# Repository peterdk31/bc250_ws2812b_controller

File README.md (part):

# Serial LED controller

A Linux daemon that renders WS2812 (NeoPixel) effects on the host and streams
the frames over USB serial to an ESP32, which just clocks them out to the strip.
All the logic — sensors, rules, effects — lives on the host, so changing
behavior never means reflashing the microcontroller.

Built for an AMD BC-250 running its case lighting from CPU temperature and load,
but nothing is board-specific. Co-authored with
[Claude](https://claude.com/claude-code) (Anthropic).

```
host (led daemon)                      ESP32              strip
sensors → rules → effect → frames ──serial──→ SPI/DMA ──→ WS2812
```

## Hardware

- An ESP32 or ESP32-C3 dev board over USB (`/dev/ttyUSB0` or `/dev/ttyACM0`).
  **Prefer the C3**: its native USB lets the firmware tell whether the host is
  actually running, so the boot animation also plays on reboots and on machines
  that keep standby power on their USB ports. A plain ESP32 can't see any of
  that over UART and only plays it after a true power cycle (see
  [How it works](#how-it-works)).
- A WS2812/WS2812B strip: data to the GPIO set as `strip.pin` (default 13), plus
  5 V and GND from a supply that can handle it (not the board's regulator; share
  grounds).
- Optionally, a momentary power button and a wire to the PSU's PS_ON# line —
  the receiver can then stand in for the PS_ON→GND jumper an ATX/FSP supply
  needs before it starts (see [Power switch](#power-switch)).
- For the BC-250 there is a small carrier PCB in
  [`hardware/bc250_carrier`](hardware/bc250_carrier/README.md): the C3 Super
  Mini solders onto it, the PSU's 10-pin Mini-Fit Jr plug goes straight onto
  a header, and the strip, button, sense wire and four PWM fan headers each
  get a labelled connector — the power switch, strip and fan wiring below, on
  one board.

## Getting started

Two things are needed on the host:

- **`g++` and `make`** to build the daemon. On CachyOS (or any Arch) they come
  in the `base-devel` package group.
- **`esptool`** to flash the receiver (plus `curl`, which is preinstalled).
  You do **not** need an ESP32 toolchain — `make flash` downloads a prebuilt
  firmware image.

```sh
sudo pacman -S --needed base-devel    # compiler + make
pipx install esptool                  # ESP32 flasher (or: pip install --user esptool)
```

On Bazzite (immutable base image) `esptool` installs the same way, but
`g++`/`make` aren't in the base image — build the daemon inside a distrobox,
or copy a prebuilt `led` binary over.

Then build, flash, and start:

```sh
sudo make install                            # daemon + systemd unit + default config
sudo make flash                              # download prebuilt firmware + flash the ESP32
sudo systemctl enable --now led-controller
```

`make flash` reads the chip (`target`, default `esp32c3`) and port
(`serial.port`) from the config; override on the command line, e.g.
`sudo make flash PORT=/dev/ttyACM0 TARGET=esp32`. It stops the service during the
write and restarts it after.

### The full BC-250 flash

Everything this repo can put on the receiver — the ATX power switch, the PWM
fans, the BLE phone remote — is described in the config, in the blocks
`power_switch`, `fans` and `ble_remote` (each has its own section below).
`make flash` bakes all three into the receiver's small settings partitions the
same way it already bakes `strip.pin`, so the full flash is the plain one:

```sh
sudo make flash
```

The config is `/etc/led-controller/config.json` when it exists, else the
repo's (`CONFIG=path` overrides). The shipped `power_switch` block is on,
with the carrier board's pins; the fan and BLE blocks ship off, and an
explicit `false` *is* written. For the power switch that matters: a receiver
whose switch is written off releases PS_ON# and cuts the machine's power (see
[Power switch](#power-switch)). Flashing from a config that has no
`power_switch` block at all leaves the chip's switch settings alone, so
delete the block, or keep it enabled, before flashing a machine whose power
already hangs on the receiver. Writing the features from one file also arms
the encoders' strictest cross-checks: a pin claimed by two blocks, or by a
block and `strip.pin`, is a hard error. Each feature's section has the `flash-pwr` / `flash-fan` /
`flash-ble` target that rewrites just that block in seconds.

Finally, edit `/etc/led-controller/config.json` for your hardware — at least
`strip.leds`, `strip.pin`, and `serial.port` — then `sudo systemctl
restart led-controller`.

To try an effect directly (stop the service first, it holds the port):

```sh
led /etc/led-controller/config.json rainbow
```

This runs unprivileged once the serial-group membership added by `make install`
is active — that takes effect on your next login; before then, prefix `sudo`.

## How it works

The daemon renders every frame and sends it over serial; the receiver only
displays what arrives. Pin and LED count travel in each frame, so the firmware
is generic and never needs reflashing for a config or effect change.

While the daemon isn't driving the line — at cold boot before it starts, and
after it exits on shutdown — the receiver plays a **boot** and **shutdown**
animation from flash. The daemon renders those too (through the same color
pipeline), records them, and uploads them once at startup; the receiver stores
them and replays them. So editing the boot/shutdown effects also needs no
reflash — just a daemon restart. A fresh, never-recorded board stays blank
until the daemon has run once and uploaded the recordings.

*When* the boot animation plays depends on the board. It always runs from chip
reset until the daemon's first frame. On USB-native chips (the C3 and friends)
it also re-arms whenever the USB host goes away and comes back — the bus
keepalives stop for a few seconds and return — which covers a reboot (shutdown
animation, dark while the host is down, boot animation as it comes back up)
and a power-on where standby VBUS kept the receiver running the whole time. A
plain ESP32's UART carries no trace of the host's state, so it shows the boot
animation only when it genuinely loses power; on a reboot it stays dark after
the shutdown animation until the daemon returns. If the power-on animation
matters to you, get a C3.

The serial baud auto-negotiates: if bytes arrive but no frame decodes, the
receiver cycles through the supported rates until frames validate, then
remembers the working rate in flash. Changing `serial.baud` just needs a
service restart.

## Flashing the receiver

The firmware is a native [ESP-IDF](https://docs.espressif.com/projects/esp-idf/en/stable/esp32/get-started/)
project under `firmware/` (no arduino-cli, no `.ino`). CI builds it for each
target and publishes merged images to GitHub Releases; `make flash` downloads
the one for `TARGET` and writes it — no toolchain needed.

```sh
sudo make flash                     # download prebuilt image + flash (default)
sudo make flash FW_RELEASE=v1.0.0   # pin a release instead of latest
```

The image is written at `0x0` and doesn't touch the NVS or LittleFS partitions,
so a reflash keeps a board's saved state.

**Building from source** is only needed to modify the firmware, or to bake a
non-default `serial.baud` / `host_timeout_ms` into it. It builds inside
Espressif's ESP-IDF container (needs `docker` or `podman` — nothing is installed
on the host, and `make receiver-clean` drops the cached image), or against a
native ESP-IDF if you set `IDF_PATH=...`:

```sh
sudo make flash-source              # build (container/native) + flash
make receiver                       # build only, no flash
```

**Clearing the board's saved state** — the reset switch when the receiver acts
as if it remembers something wrong. Each erases one partition region; the app
and the power-switch wiring (`pwrcfg`) are untouched:

```sh
sudo make clear-nvs                 # remembered baud + strip geometry
sudo make clear-recordings          # stored boot/shutdown animations
```

The daemon re-uploads the recordings on its next start (and the receiver
re-formats the partition), so `clear-recordings` is also how you get past a
stale or half-written slot that the skip-unchanged hash check would otherwise
keep. As with flashing, esptool resets the chip — see the caveat under
[Power switch](#power-switch).

### Receiver debug log

The receiver has no console (the link is the daemon's), so it keeps a small log
ring in RAM and hands it back over the link on request. Set

```jsonc
"serial": { "debug_log": true }
```

and its lines appear in `journalctl -u led-controller` — the recording uploads
and where they went, boot/shutdown replays, host-gone/host-back transitions, the
strip blanking on timeout, and the power switch's own decisions. The ring is in
RAM on a board running from 5VSB, so events logged while the host was down (a
follow-down, a boot replay) drain once the daemon is back. With the flag off the
daemon never asks and the receiver never sends a log line — the only thing it
ever says unprompted is a power-button request (see
[Power switch](#power-switch)).

## Configuration

`/etc/led-controller/config.json`. The first half describes the receiver — the
chip, the link, and everything it does on its own when the daemon isn't
running — the second half the host's rendering:

```jsonc
{
    "target": "esp32c3",        // chip to build/flash for (esp32, esp32c3, ...)
    "serial": {
        "port": "/dev/ttyUSB0", // "none" or "" (or LED_PORT=none) runs headless;
        "baud": 921600,         // omitting the key defaults to /dev/ttyUSB0
        "debug_log": false      // drain the receiver's log to journalctl
    },
    "host_timeout_ms": 5000,    // receiver blanks after this long with no frame —
                                // baked into the firmware by `make flash-source`
                                // only; the prebuilt image always uses 5000
    "power_on": { ... },        // boot/shutdown animations the receiver replays
    "shutdown": { ... },        // (standalone effects only, see below)

    "power_switch": {           // the ATX power button, see Power switch
        "enabled": true,            // enabled + pins: flash-time (make flash-pwr)
        "hold_seconds": 2,          // hold this long for a hard cut     ┐ the four tunings:
        "boot_timeout_seconds": 10, // rail not up by then = release PS_ON# │ live (reload, or
        "sense_low_mv": 800,        //                                     │ the phone's cog
        "sense_high_mv": 2000,      //                                     ┘ on the Power tab)
        "pins": { "ps_on": 3, "button": 1, "button_gnd": null, "sense": 2, "led": 8,
                  "wake": null },   // wake: an OpenPuck's power-on pulse, see Power switch
        "short_press": "systemctl poweroff" // what the daemon runs on a short
                                    // press; null = ignore it
    },
    "ble_remote": {             // the phone power button + dashboard, see BLE remote
        "enabled": false,
        "name": "BC250",
        "token": ""                 // 8-16 chars; readable by anyone with a shell here
    },
    "fans": [                   // the fans, see Fans — each an input, a curve
        { "name": "pump", "output": "header1",               // and an output (a receiver
          "input": "fallback", "fallback": 65, "boost": 100 }, // header, a pin, or the
        { ... }                                              // host's own pwm output)
    ],

    "strip": {
        "leds": 58,
        "pin": 13,              // ESP32 GPIO driving the strip
        "reverse": false,       // flip so LED 0 is at the far end
        "brightness": 0.2,      // 0..1, linear
        "gamma": "2.2",         // one value, or three ("2.0 2.2 2.4") per R/G/B
        "white_balance": "ffb0f0" // RRGGBB neutral-white gain; ffffff = off
    },
    "sensors": [ ... ],         // hwmon candidates, see Sensors
    "rules": [ ... ]
}
```

Configs from before September 2026 had an `esp32` block and a `sinks.serial`
one; the daemon names the old key and what it became, and exits, rather than
run on a half-read file.

### Checking a config

```sh
led --check /etc/led-controller/config.json   # or: make check
```

Would the daemon start on this file, and is it the file you meant to write?
The check parses it and runs every block through the same validation the
daemon does at startup — retired keys, the fans block, the rules and their
conditions and effect names, the boot and shutdown recordings (rendered, so a
segment that can't record is caught here) — and then the things the daemon
would run on but nobody could have intended: a key that isn't one inside
`serial`, `strip`, `power_switch`, `ble_remote`, a rule or a recording
segment (with a "did you mean" for a near miss), a value of the wrong type, a
color that isn't `RRGGBB`, a LED count over the receiver's 100, an inverted
sense hysteresis, an enabled `ble_remote` without a token. Each is a line
naming the key; any of them fails the check (exit 1). A `note:` line is
something to look at that may be intended — a top-level key the daemon
doesn't read by name (effects see every top-level key as a shared default
setting), or a rule below a catch-all that can never be reached — and
doesn't fail it. It opens no port and sends nothing; the sensor lookups only
say "not found yet" on a box without them.

`make install` runs the check on the deployed file with the freshly built
daemon before it swaps the binary and restarts the service, so a key the new
version retired is reported while the old daemon still runs, not as a crash
loop after; `make install CHECK=0` skips that.

### Live reload

The running daemon watches its config file and picks up a save within a
second or two — rules, effects, sensors, strip settings, the fans block —
with no restart. A change confined to the `fans` or `power_switch` blocks
leaves the running effect alone; anything else drops the current effect and
the matching rule starts afresh (a crossfade on the strip, like any other
switch). `systemctl reload led-controller` (SIGHUP) does the same
immediately. A file that doesn't parse or validate is reported in the journal
and the running config is kept, so a typo costs a log line rather than a
crash loop; fix it and save again. Two things still need more than a reload:
the `serial` block, because the port is opened once (the daemon says so when
it changes; restart), and anything flash-time on the receiver — the power
switch's pins and enable, the board's fan header map, `ble_remote` — which
is `make flash`'s business (the fans' outputs are not: a reload moves them). The power switch's four tunings and `short_press` are
not flash-time: a reload pushes the tunings to the receiver and changes what
a press does at once. Editing `power_on`, `shutdown` or `strip` re-renders
and re-sends the boot and shutdown recordings, which holds the strip for
about a second. Edits from the phone's dashboard take a shorter path: they
are applied live and written into the file by the daemon itself (`fans`,
`strip`, a scene rule's `color`/`level`, the `power_switch` tunings and
`short_press`), which then treats the file's new mtime as its own doing
rather than a change to reload.

### Tuning the colors

`brightness`, `white_balance`, and `gamma` fold into one per-channel lookup
table applied on the host, so they cost nothing per frame.

How to read the values — every knob is per-channel, red green blue:

```
white_balance "b4b0f0"          gamma "1.9 1.8 1.7"
               ││││└┴─ blue            └┬┘ └┬┘ └┬┘
               ││└┴─── green          red green blue
               └┴───── red
```

Two rules cover every adjustment:

- **White balance scales a channel the same at every level.** Lower a pair →
  less of that color, from full white down to the dimmest glow. `ff` = leave
  the channel alone.
- **Gamma changes how a channel *fades*.** A higher number makes that channel
  die away faster as colors dim; full-on and off never move. `2.2` is
  neutral; you only need three different numbers when a tint appears *only*
  at low levels.

So: name the color the white is leaning toward, then move that channel —
down in `white_balance` if the tint is there at full brightness, up in
`gamma` if it only creeps in as things get dim.

Dial the knobs in by symptom, in this order:

1. **Everything too bright or dim for the room** → `brightness` (0..1).
2. **Full white looks tinted** → `white_balance`: lower the channel(s) of
   the tint. White leans green → lower the middle pair (`ffb0f0`). This is
   the strip+diffuser calibration; start from the diffuser table below.
3. **Full white is neutral, but dim white picks up a tint** →
   per-channel `gamma`: raise the tint's channel so it fades faster (dim
   white leans blue → `"2.2 2.2 2.4"`) — or equivalently lower the channel
   that's going missing (dim white leans blue because red drops out →
   `"2.0 2.2 2.2"`).

The `solid` effect exists for exactly this — it puts up a fixed test field
through the normal correction pipeline:

```bash
led /etc/led-controller/config.json solid    # full white: judge white_balance
```

Look, adjust the config, run again. For the gamma step you need *dim* white;
a forced effect has no rule settings, but effects fall back to top-level
config keys, so temporarily add `"level": 0.25` at the top level of the
config (next to `"strip"`) and run `solid` again. Remove it when done.

**From the couch, with the BLE remote:** the shipped config's first rule is
the same test field as a switch — a static color with a level, which doubles
as a plain light when it isn't tuning anything —

```jsonc
{ "if": "file:/tmp/led-static-color", "effect": "solid", "hold": 0,
  "settings": { "color": "ffffff", "level": 1.0 } }
```

— and the phone's dashboard shows every such `file:` rule as a **scene**
with a switch (README [BLE remote](#the-dashboard)). Switch "solid" on, drag
the white-balance sliders on the LEDs tab while looking at the strip
(each release applies to the live strip at once and lands in the config's
`strip` block), pull the scene's `level` slider down for the gamma step,
switch it off. The color picker on the scene changes the rule's `color`, so
the same switch tests a pure red or a warm white. Any `file:` rule with a
`color` or `level` setting gets the same controls; one without is just a
switch (the `/tmp/led-night` rule below, say). Put these rules first so they
win over everything else while on.

`white_balance` is the *total* correction — strip and diffuser combined into
one measured value. Starting points per diffuser (always confirm against
`solid` white):

| Diffuser | `white_balance` | Why |
|---|---|---|
| none / clear cover | `ffb0f0` | just the strip's own green excess |
| white (milky) | `ffb0f0` | near-neutral filter; scatters but barely tints — trim blue a touch (`ffb0e0`) if white reads cool |
| black / smoked film | `b4b0f0` | dark film passes red most, so take the bare-strip value and pull red down ~30% on top of it. Films vary a lot: one measured black window film landed at `b4ffff` instead — its green/blue cut cancelled the strip's own green excess. Pair with per-channel gamma (e.g. `"1.9 1.8 1.7"`) if dim white still drifts |

Low brightness costs no smoothness: the corrected values ride the wire with 8
extra fractional bits and the receiver rounds them away with a temporal dither
at its own strip-refresh rate (several hundred Hz — far above flicker fusion),
so dim gradients glide instead of stepping or shimmering. There is nothing to
configure; the old `dither` key is gone (this needs receiver firmware from the
same version — reflash once after updating). A change to `strip` re-renders
the boot/shutdown recordings so they carry the new colors — on a hand edit as
part of the reload, after a phone edit ten seconds after the last slider
moved (each re-render holds the strip for about a second).

### Sensors

`sensors` is an ordered list of `chip:label` hwmon candidates; the first present
wins (a bare chip name means its `temp1_input`). Used by `temp` conditions.
The daemon keeps rescanning until one appears. The default
covers the BC-250 (`k10temp:Tctl`, then the NCT6686D under either nct driver).
Two more kinds of candidate take the same slot: `pmbus:CPU VRM` / `pmbus:GPU VRM`
read the BC-250's VRM controller over I2C, and `file:/path` reads a file
holding one temperature — both described under [Fans](#fans), where they are
also fan sources.

### Rules

Evaluated top to bottom every 0.5 s; the first rule whose `if` holds wins. A rule
without `if` always matches (put a catch-all last). No match → strip dark.

```jsonc
{
    "if": "proc:gamescope & temp>75",
    "effect": "ember",
    "hold": 5,                       // min seconds since last switch (default 0)
    "for": 3,                        // condition must hold this long to count (default 0)
    "settings": { "speed": 1.4 }     // effect-specific
}
```

Switches crossfade over the top-level `crossfade_ms` (default 600; 0 =
instant). `for` is an on-delay on the condition: it has to have held for that
many seconds before the rule matches, so a brief load spike never starts a
load rule. Dropping out is immediate. `hold` is the blunter guard: no switch
*into* this rule until that long after the last switch, whatever the
conditions did meanwhile.

### Conditions

| syntax | true when |
|---|---|
| `always` | always |
| `temp>N` / `temp<N` | sensor temperature above/below N °C |
| `cpu_load>N` / `cpu_load<N` | CPU busy above/below N % (bare `cpu_load` = `>20`) |
| `gpu_load>N` / `gpu_load<N` | amdgpu busy above/below N % (bare `gpu_load` = `>20`) |
| `proc:NAME` | a process with that name is running (15-char kernel limit) |
| `steam_dl` | a Steam download is actively moving bytes |
| `steam_launch` | a game launch is in a counted step — processing Vulkan shaders, verifying files (needs the debug port) |
| `steam_achievement` / `steam_achievement<N` | a Steam achievement unlocked in the last 5 / N seconds (needs the debug port) |
| `audio_playing` | system audio is actually playing (see below) |
| `file:/PATH` | the file exists |
| `!COND` | negation |
| `A & B` | both hold |
| `A \| B` | either holds (`&` binds tighter; no parentheses) |

`file:` is the external control surface — `touch /tmp/led-night` to switch modes,
`rm` to switch back. A rule whose whole condition is one `file:` path is also
a **scene** on the phone's dashboard ([BLE remote](#the-dashboard)): a switch
the daemon flips by creating or removing that file, with a color picker or a
level slider when the rule's settings carry `color` or `level`.

The `progress` effect turns the strip into a live progress bar for whichever
`"source"` its settings name — `steam_dl` (a download) or `steam_launch` (a game
launch processing its shaders) — with a celebration pulse at 100%. The rule's
condition is the same name, so the bar shows exactly while there's something to
show; give each its own palette (the default config does) to tell them apart.
`STEAM_FAKE_PERCENT` / `STEAM_FAKE_LAUNCH` preview them without Steam: a number
holds a static bar, `ramp20` climbs 20 %/s and celebrates.

Downloads work without the debug port too (percent driven by network
throughput). Reading other
users' Steam libraries needs the daemon running as root (the systemd unit does).
Each app of an install (the game, Steamworks redistributables, Proton, shader
pre-cache) fills its own bar, one after the other.

For exact progress the daemon reads Steam's own numbers — the ones its Downloads
page shows — over Steam's remote-debugging port, `"steam_debug_port": 8080` (on
by default; `null` turns it off). That needs Steam's remote debugging on: an
empty `.cef-enable-remote-debugging` file in the Steam directory
(`~/.local/share/Steam/`), which `make install` creates for every Steam user
while the key is set (Decky Loader creates it too). Restart Steam once after.
`make steam-debug-uninstall` (also part of `make uninstall`) removes the files
`make install` created, never one that was already there; set the key to `null`
as well, or the next install puts them back.

The debug port also feeds `steam_launch` (the launch dialog's counted steps) and
`steam_achievement`: Steam's own unlock toast, counted by the daemon's hook,
plays the `achievement` effect — a bloom at `origin` throwing a gold front along
the strip, glinting, then easing to dark. An unlock fewer than `rare_below` % of
players have burns in `rare_palette` instead. `STEAM_FAKE_ACHIEVEMENT=6` fires
a fake unlock every 6 s (every other one rare). `led <config> --steam-status`
shows what the hook sees, and which of Steam's functions a Steam update took
away.
The bar then follows Steam's percent, and a pause or finish shows at once. It uses
Steam's internal JS API (the one Decky plugins use), so a Steam update can break
it; whenever the port doesn't answer the daemon falls back to the estimate above
and says so in the journal. The port is localhost-only, but anything running on
the machine can drive the Steam client through it. `led <config> --steam-status`
shows which source is in use and what Steam reports.

The `audio_*` effects visualise what's playing (combine them with `cycle` for
variety — they share one capture stream and auto-gain, so hopping between them
is seamless). The effects capture samples by spawning `parec` (or
`pw-record`) on the default sink's monitor while active; running as root
(the systemd unit does) lets it find the user session's PipeWire socket under
`/run/user/`.

The `audio_playing` condition costs nothing while the system is silent (one
procfs read per tick). Once anything is audible it asks the sound server for
its playback stream list (`pactl -f json list sink-inputs`, spawned
asynchronously about once a second): an uncorked stream means playing, corked
or none means paused/stopped. That verdict is immune to quiet passages inside
the music and reacts to pause/resume within a second or two. It is also the
only source of truth: if the list can't be fetched while audio is audible
(no `pactl`, no reachable session), the condition stays false and a note is
left on stderr. Placing the rule *below* the `load` rule means load takes the
strip whenever it's active and music has it otherwise — first matching rule
wins.

## Effects

| name | description | key settings (defaults) |
|---|---|---|
| `alarm` | urgent heartbeat throbbing from the center | `color` (ff0000), `pulses_per_second` (2) |
| `audio_music` | audio-reactive bloom from the center: loudness sets its reach, bass pumps it and sends crests to the tips | `palette` (4a00b4,e02090,ff9c28), `pulse` (0.8), `gain_seconds` (6) |
| `audio_ripple` | audio-reactive: each bass hit sends a wave crest with a luminous wake racing from the center to the tips, reflecting back off them, colors walking the palette per beat | `palette` (0030a0,00c0e0,8040ff), `travel_seconds` (1.0), `sensitivity` (1.0), `reflect` (0.6) |
| `audio_spectrum` | audio-reactive liquid analyzer: a spring-loaded bar grows from the strip start with the loudness, a meniscus shine on its tip, bass pumping its base and treble its tip, a peak dot falling back with a comet tail between hits | `palette` (00e6b4,3a56ff,ff2e88), `pump` (0.7), `bounce` (0.6), `peak_color` (ffffff) |
| `achievement` | one shot: a bloom throws a glinting gold front along the strip, then eases to dark; rare unlocks in their own palette | `palette` (ff8a00,ffc040,fff0b0), `rare_palette` (ff3cac,8a4bff,38c8ff), `rare_below` (10), `origin` (0.5) |
| `aurora` | slow drifting color curtains walking a palette | `palette` (10ff80,10a0ff,8040ff), `speed` (1.0) |
| `boot` | calm bloom from the center into a full wash, then exhales into a dim hold | `intro_seconds` (7), `color` (ffffff) |
| `breathe` | palette wash on a slow breath with a drifting bright band | `palette` (0d4a44,30e090), `period_seconds` (3.5) |
| `button_off` | experimental: the lit strip collapses into the power button | `duration_seconds` (1.4), `color` (ffffff), `reverse` (true) |
| `button_on` | experimental: light spills out of the power button, then pulses | `spread_seconds` (2.5), `period_seconds` (4), `color` (ffffff) |
| `caustics` | underwater light caustics: two multiplied noise fields carve bright wandering filaments that merge and dissolve | `palette` (020818,004060,00b0c0,a0fff0), `sharp` (1.5), `gain` (3.2) |
| `comet` | Larson scanner with a fading tail, optional mirror | `palette` (8040ff,30c0ff), `sweeps_per_second` (0.7), `tail_pixels` (8) |
| `cycle` | rotates through a list of other effects | `period_seconds` (30), `effects` (list) |
| `drift` | soft palette glows wandering over a dark base | `palette` (2858ff,30d0b0), `blobs` (3), `speed` (1.4) |
| `ember` | slow warm aurora-style flow through an ember palette | `palette` (2a0a00,ff7d1e), `speed` (1.4) |
| `ink` | drops of ink recolor the whole strip in slow sweeping fronts, a glistening rim on each leading edge | `palette` (6a00ff,0080ff,00d0a0,ffb000,ff2060), `period_seconds` (10), `spread_seconds` (4) |
| `lava` | lava lamp: soft blobs drift, meet and merge into hotter spots | `palette` (ff0050,ff5a00,ffd000,00e5ff,7a00ff,ff00d0), `blobs` (4), `speed` (5.0) |
| `load` | CPU/GPU bars from center over a palette wash, each with a heartbeat that quickens under load; each side's palette window slides toward the hot end with its load | `palette` (00e0c0,2060ff,a040ff,ff4060,ff9000), `heat_span` (0.45), `color_drift` (0.3), `pulse` (0.5) |
| `load_boil` | CPU/GPU load as a lava lamp: each half's blobs boil harder and shift toward the palette's hot end with that side's load | `palette` (00e0c0,2060ff,a040ff,ff4060,ff9000), `blobs` (2), `boil` (2.5) |
| `orbit` | binary stars: glow pairs orbit a shared center, whipping through conjunctions that bloom white-hot | `palette` (1030ff,00d0ff,c080ff,ff40a0), `pairs` (2), `origin` (0.5) |
| `pendulum` | pendulum wave: each LED swings once more per period than its neighbour, so the strip drifts from one shared swell through travelling waves and braids and marches back into step | `palette` (2040ff,00d0c0,a040ff,ff4090,2040ff), `period_seconds` (60), `swings` (15), `origin` (0.0) |
| `plasma` | drifting sines + noise walking a palette | `palette` (0040ff,00d0a0,c040ff,0040ff), `speed` (1.4) |
| `progress` | live progress bar for a `source` (`steam_dl`, `steam_launch`), pulse at 100% | `source` (steam_dl), `palette` (d4009c,ff5a1e,ffd23c), `done_color` (00ff66) |
| `pulse` | soft palette rings expanding from the center | `palette` (5028ff,30d0ff), `period_seconds` (4) |
| `rainbow` | scrolling hue cycle with shimmer | `cycles_per_second` (0.9) |
| `shoreline` | waves roll in from both ends, decelerating and whitening into foam as they break at the center | `palette` (003048,00a090,60e0c0), `period_seconds` (6), `foam_color` (ffffff) |
| `shutdown` | CRT-style collapse to a point, then a slow phosphor fade | `duration_seconds` (5.0), `color` (0028ff) |
| `silk` | tide through a drifting warp field: color bands stretch, buckle and fold like fabric in a breeze | `palette` (3a1078,c03080,ff9040,20b0c0,3a1078), `fold` (0.5), `sheen` (0.3) |
| `solid` | fixed color everywhere — the color-calibration test field, or a plain static light | `color` (ffffff), `level` (1.0) |
| `tide` | a palette gradient sliding and breathing | `palette` (102060,1890d0,30d0a0,8040ff,102060), `speed` (1.4) |

Colors are `"RRGGBB"` or `"#RRGGBB"`; a `palette` is several separated by
non-hex (`"2a0a00, ff7d1e"`), spaced evenly and blended in RGB. Every effect
also takes `frame_ms` (delay between frames; default 16 ≈ 60 fps).
Settings resolve per-rule first, then top-level config, then the defaults above.

### Boot & shutdown animations

Set `power_on` / `shutdown` to any standalone effect, or a `sequence` played
into one recording — typically a one-shot intro into a looping idle:

```jsonc
"power_on": {
    "sequence": [
        { "effect": "boot",    "record_seconds": 4,
          "settings": { "intro_seconds": 3, "color": "ff7818" } },
        { "effect": "breathe", "record_seconds": 5, "loop": true,
          "settings": { "palette": "2a0a00,ff7818", "period_seconds": 5 } }
    ]
},
"shutdown": { "effect": "shutdown", "settings": { "color": "0028ff" } }
```

The last segment's `loop` decides the tail (loop from its first frame, else hold
the last frame); earlier segments play once. For a seamless loop make the
looping segment's `record_seconds` a whole multiple of its period. The whole
recording replays at one rate — the first segment's `frame_ms` — so a later
segment's own `frame_ms` has no effect on replay. Finite
effects (`shutdown`) record to completion; open-ended ones (`boot`) record for
`record_seconds`. Unchanged recordings aren't rewritten to flash (a hash is
compared), so wear is near zero. `cycle` can't be a slot (it needs the JSON
config).

Preview a slot exactly as the receiver will replay it, without hardware:

```sh
make virtual-strip && ./virtual-strip                    # one terminal
LED_PORT=none ./led config.json --preview power_on       # another
```

## Power switch

An ATX/FSP supply (like the BC-250's FSP500-30AS) doesn't start until its
PS_ON# line (the green wire) is pulled to ground — normally a permanent
jumper. With the receiver powered from the PSU's **5VSB** standby rail, it can
drive that line instead and act as the machine's power button
(after [Thunkar/bc250-esp32-switch](https://github.com/Thunkar/bc250-esp32-switch),
minus its WiFi/BLE):

- **Press** the button while off → PS_ON# is sunk to ground, the PSU starts,
  the board boots. It fires on the press itself, not on the release, so that
  keeping it held afterwards is free to mean the failsafe below.
- **Short press** while the machine is up → the ordinary PC power-button
  gesture: the OS is asked to shut itself down gracefully. The receiver can't
  do that itself, so it asks over the link and the daemon runs the
  `power_switch.short_press` command (`"systemctl poweroff"`); the machine
  then powers itself off and the sense wire's follow-down releases PS_ON#.
  With `short_press` set to `null` the press is ignored (and the journal
  says so). If nobody answers within 3 s
  — daemon down, no OS yet, feature off — the request is dropped and the
  feedback LED blinks fast for a moment, because otherwise an unheard press
  looks exactly like a broken button. Nothing about this path touches PS_ON#:
  the worst case is a machine that stays on.
- **Hold** for 2 s while on → PS_ON# is released — a hard power-off for a
  wedged machine, and the answer to an OS that accepts the graceful request and
  then hangs. (Only a press that began while the machine was already up can do
  this: the press that powered it on never turns it back off, however long it's
  held.)
- With the **sense** wire (BC-250: TPMS1 pin 9, ~2.9 V while the board is
  up): a graceful OS shutdown is followed down (the sense line drops, the
  receiver releases PS_ON# so the PSU turns off too), and a board that never
  comes up within 10 s releases the PSU instead of leaving it energized.
  The wire is optional but strongly recommended — without it both are
  skipped, and after every OS shutdown the PSU stays energized, holding
  PS_ON#, until a 2 s long-press; what's left is less a power button than a
  toggle that sticks on.
- **Keep holding the button** → the failsafe: while it is physically held the
  sense line cannot power anything off. Follow-down is suppressed, and the boot
  timeout is parked, counting its 10 s from the release instead of from the
  power-on. This is the way out of a mis-wired sense line, which is otherwise
  self-sealing: a sense pin that reads low while the board is really up (wrong
  pin, wire fallen off, thresholds wrong) makes the boot timeout cut the PSU
  ~10 s into every boot, so the machine can never stay up long enough to
  reflash the config that would fix it. Press to power on, keep your finger
  down, and the machine stays up while you reflash — including *through* the
  reflash: a receiver that comes up with the button already held adopts that
  press as the failsafe, and won't read it as a fresh 2 s force-off either.
  The sense line is still sampled and logged while held (see the debug log
  below) — that log is how the right pin and thresholds get found.

Wiring (the shipped `power_switch.pins`, for the ESP32-C3; `null` = not wired):

| receiver pin | connects to |
|---|---|
| GPIO3 (`ps_on`) | gate of an N-channel MOSFET that sinks PS_ON# to ground (see note below) — **not** PS_ON# directly |
| GPIO1 (`button`) | momentary switch terminal A (internal pull-up, pressed = low) |
| `button_gnd`: `null` when the switch is wired to a real GND (the carrier board), else e.g. GPIO21 | switch terminal B — driven low as a local ground, so the button needs no run to a real GND. (GPIO21 is U0TXD: free while the host link is USB) |
| GPIO2 (`sense`, `null` = not wired) | optional board-power sense, e.g. BC-250 TPMS1 pin 9, which is the board's main **3.3 V rail**. Emphatically *not* pin 15 (`3VSB`): that stays up whenever PS_ON# is held, so it reads like a working sense wire and then never fires follow-down or the boot timeout. Read as an averaged ADC voltage with hysteresis (`sense_low_mv` / `sense_high_mv`); the ADC saturates near 3.1 V, so a healthy rail logs ~2.9–3.1 V |
| GPIO8 (`led`, `null` = none) | optional feedback: the board's own little LED *blinks* while the button reads pressed (and through a wake pulse), so the wiring can be eyeballed without a PSU. GPIO8 is the plain onboard LED on common C3 dev boards; a blink shows regardless of the LED's polarity |
| `wake` (`null` = not wired; GPIO20 on the carrier's J11) | optional **wake input**: a 3.3 V active-high pulse from another device that wants the machine on — see *Waking from an OpenPuck* below. Internal pull-down; a rising edge while OFF powers on, and a pulse in any other state is dropped, so it can never shut anything down. Because it can do nothing else, this is the one pin that also **moves at runtime**, like the tunings: the daemon pushes `pins.wake` at startup and on a reload, and the phone's power settings pick it from the receiver's free pins (see [The dashboard](#the-dashboard)) |
| 5VSB + GND | PSU standby rail, so the receiver runs while the machine is off — **read the warning below before also plugging in USB** |

> ⚠️ **Critical — 5VSB and USB at the same time.** In this role the receiver
> is powered from 5VSB *and* still plugged into the host's USB for the LED
> link. That is two hard-paralleled 5 V supplies: most dev boards tie the USB
> connector's VBUS straight to their 5 V pin, so whichever rail sits higher
> pushes current into the other with nothing to limit it. Whenever the
> machine is off — the normal state for a power button — that means the
> receiver back-feeds the host's **dead** USB port continuously: current
> flows backwards through the port's VBUS circuitry (which is not designed
> for it and can be damaged) and phantom-powers part of the motherboard's
> 5 V rail off the PSU's small standby supply. **Cut or unpin the 5 V wire
> (red) in the USB cable**; keep D+, D− and GND. The receiver then runs
> solely from 5VSB and USB still works fully as a self-powered device —
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
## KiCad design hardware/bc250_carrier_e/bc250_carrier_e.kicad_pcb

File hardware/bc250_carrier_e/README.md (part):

# BC-250 carrier board (rev E)

Rev E is the same carrier as [rev D](../bc250_carrier/README.md), with the same
parts, nets and firmware, laid out differently: **every plug sits on the left,
the PSU header at the board's right-hand end, and the module directly beside
it.** The fans run down the left edge, the breakouts, the button and the strip
sit in a column beside them, and no signal has to cross the PSU plug's zone.
76.8 × 34.5 mm (rev D: 80 × 34.5), two layers.

*`make pinout` → `pinout.png`, drawn from `generate.py`'s geometry. Open it
at full size for soldering.*

Both revisions stay buildable side by side: rev D in `hardware/bc250_carrier/`,
rev E here. The tools (`check.py`, `drc.py`, `fill.py`, `preview.py`,
`fab.py`, `zoom.py`) are copies of rev D's and work the same way; only
`generate.py` and `pinout.py` differ.

## Layout

Left to right:

- **The four fan headers** stacked down the left edge, 9 mm apart, pins
  G · 12V · T · PWM left to right, lock ramps facing down. Their 12 V and GND
  are two bars down the column.
- **Column C**, top to bottom: the power breakout **J14**, the button **J9**,
  **R1**, **Q1** and the strip **VH (J3)**. The fan PWM lines cross it in
  three lanes between J14 and J9 (FAN4's between Q1 and the VH).
- **J11** (the sense wire and the spare GPIOs), right beside the module's
  left pad column.
- **The Super Mini** in its two sockets (J12, J13), USB-C at the top edge.
  Nothing sits under it, so it can still be soldered flat instead of
  socketed.
- **The PSU header (J1)** directly beside the module at the right-hand end,
  the same right-angle Mini-Fit Jr as rev D, facing the same way: the plug
  lies flat over the board's right quarter and its wires leave over the top
  edge. Everything above the header is the **plug zone**: tracks only,
  nothing taller than the solder mask.

The module's right pads (DIN, GATE, BTN, GPIO0) face the PSU header, so their
lines go round the module: down the gap between it and the header (6.7 mm between their pin columns) (or
inside its right pad column) and west along the bottom edge under its antenna
end, next to the strip's 3 A feed from the header's 3.3V pin.

No mounting holes: the plug zone has to stay flat and every other spot is
taken. The repo's case isn't used with this board.

## What is on it

The same parts as rev D (see its ordering table; J11 and J14 are still cut
from 2 × 8 pin headers and left off assembly orders).

The rev C fan headers (Ckmtw W-2510S04P, KF2510) fit the same holes, but
only just: their body is 12.7 mm long (the Molex's about 10.2), so FAN2's
reaches about 0.2 mm into J9's housing and FAN3's and FAN4's about 0.15 mm
into J3's. Dry-fit first: fit J9 and J3, then push each fan header towards
the left edge while soldering it (the pins have about 0.15 mm of play in
their holes); if one still won't sit flat, file about 0.3 mm off the end
facing column C. Their lock ramp spans all four pins, so it needs cutting
down as on rev C; fit them with the ramp facing down the board, as the
silkscreen shows. A fan plug as long as 12.7 mm would just touch J9 or J3
when plugged in (not checked on a real plug).

| ref | part | where |
|---|---|---|
| J5–J8 | four Molex 47053-1000 fan headers, stacked, pins G 12V T PWM left to right | left edge |
| J14 | 2 × 3 power breakout, turned: three columns 3V3, 12V, 5VSB, two pins each | column C, top |
| J9 | JST-XH 4-pin button connector: pins 12V, GND, NO, C left to right | column C |
| R1, Q1 | 100 kΩ; 2N7000 on the wide TO-92 footprint (S G D left to right) | column C |
| J3 | JST-VH strip connector, turned 180: GND, DIN, 3.3V left to right | column C, bottom |
| J11 | 2 × 6: SENSE + five spare GPIOs, GND beside each (as rev D) | between column C and the module |
| U1 on J12 + J13 | ESP32-C3 Super Mini in two 1 × 8 low-profile sockets | beside the PSU header |
| J1 | PSU header, Mini-Fit Jr 5569-10A2 right-angle | right-hand end |

## Wiring

| connector | pins | goes to |
|---|---|---|
| PSU J1 | as rev D ([the PSU header](../bc250_carrier/README.md#the-psu-header)) | the FSP500-30AS 10-pin plug, straight on |
| STRIP J3 | 1 `3.3V`, 2 `DIN`, 3 `GND`; pin 1 is the **right** pin | the WS2812B strip; DIN is GPIO4 |
| BUTTON J9 | 1 `12V`, 2 `GND`, 3 `NO`, 4 `C`; pin 1 is the **left** pin | the illuminated button as on rev D: 1–2 the ring LED (12 V), 3 the normally-open contact → GPIO1, 4 the switch's common (a real GND) |
| J11 | 1 `GND` / 2 `SENSE`, 3 / 4 `GPIO8`, 5 / 6 `GPIO9`, 7 / 8 `GPIO20`, 9 / 10 `GPIO21`, 11 / 12 `GPIO0` (odd pins GND) | as rev D: the sense wire (BC-250 TPMS1 pin 9) on pin 2; OpenPuck `017` → pin 8, its GND → pin 7 |
| J14 | columns left to right: pins 1+2 `3.3V`, 3+4 `12V`, 5+6 `5VSB` | optional rail breakout; an OpenPuck's BAT goes on 5VSB (pin 5 or 6) |
| FAN1 J5 … FAN4 J8 | left to right: `G`, `12V`, `T`, `PWM` | standard 4-pin fans, tach unconnected; FAN1..4 = GPIO 5, 6, 7, 10 = `header1..4` in the config, top to bottom. The lock ramps face down the board |

The config is unchanged from rev D: the same `power_switch` pins, the same
fan headers, `strip.pin` 4.

## Routing

The rule from rev D holds: on the back, where every joint is soldered, **12 V
passes no pad of 5VSB, GATE, 3.3V, PS_ON# or any GPIO within 1 mm.** The
only 12 V on the back is the PSU header's own pin 4-5 tie (J14's pins sit
0.84 mm apart at the 2.54 mm pitch, as on any header). A slipped bridge on the
back can short a rail to ground or switch the PSU, never feed 12 V into the
module. On the front, under FAN1's plastic, the top-edge 12 V passes FAN1's
PWM pin at 0.6 mm.

- **12 V** leaves the PSU header's pin 4 straight up through the plug zone
  and runs along the top edge on the front (2 mm, ~3.5 A), then down the
  fans' 12V pins as a bar. J14's 12 V column taps it, and J9's LED is fed
  from that column on the front.
- **The fans' ground** runs along the top edge on the back, right under the
  12 V, and down the fans' G pins, so the fan current's loop is one narrow
  strip. At the other end it drops into the PSU header's pin 2. A **ground
  spine** runs down the back of the gap between the module and the header,
  from the top edge to the bottom edge; the module's GND pad joins it, a
  branch goes over pin 1 into pin 2, and the strip's 3 A return comes east
  along the bottom edge from the VH's GND pin into it. J9's, J11's, Q1's and
  R1's grounds have a web of their own down column C into the VH's GND pin,
  and the ground fill on both layers, stitched with ground vias, ties in
  everything else.
- **3.3V** (3 A) leaves the header's pin 6 as a 2.5 mm track west along the
  bottom edge on the front, into the VH's pin 1. On from there, narrower, it
  runs under the VH's other pins to the gap by the fans and up it into J14's
  3V3 column.
- **5VSB** runs from the header's pin 3 up through the plug zone into the
  module's 5V pin (front), and on over the module's top to J14's 5VSB column.
- **The fan PWM lines** run west on the back: FAN1's to FAN3's off the
  module's top three pads, in three lanes under J14 to the gap by the fans,
  then up or down into each pin 4. FAN4's goes down between J11 and the
  module, under J11 and over the VH's pins.
- **DIN** goes down the back inside the module's right pad column (0.5 mm
  from the pads, clear of the antenna zone), west along the bottom and up
  into the VH's pin 2. **SENSE** goes up the same lane on the front and over
  the module's top into J11. **GPIO0** drops off its pad and goes west under
  the module's end into J11's bottom row.
- **BTN** and **GATE** go east off their pads, down the gap by the header,
  west along the bottom edge and up between column C and J11: BTN under J9
  into its pin 3, GATE into R1's pin 1 and on to Q1's gate. **PS_ON#** leaves
  the PSU header's pin 8 through the gap between its pin rows on the back,
  changes to the front through a via just past the header's left end and
  follows them into Q1's drain.

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
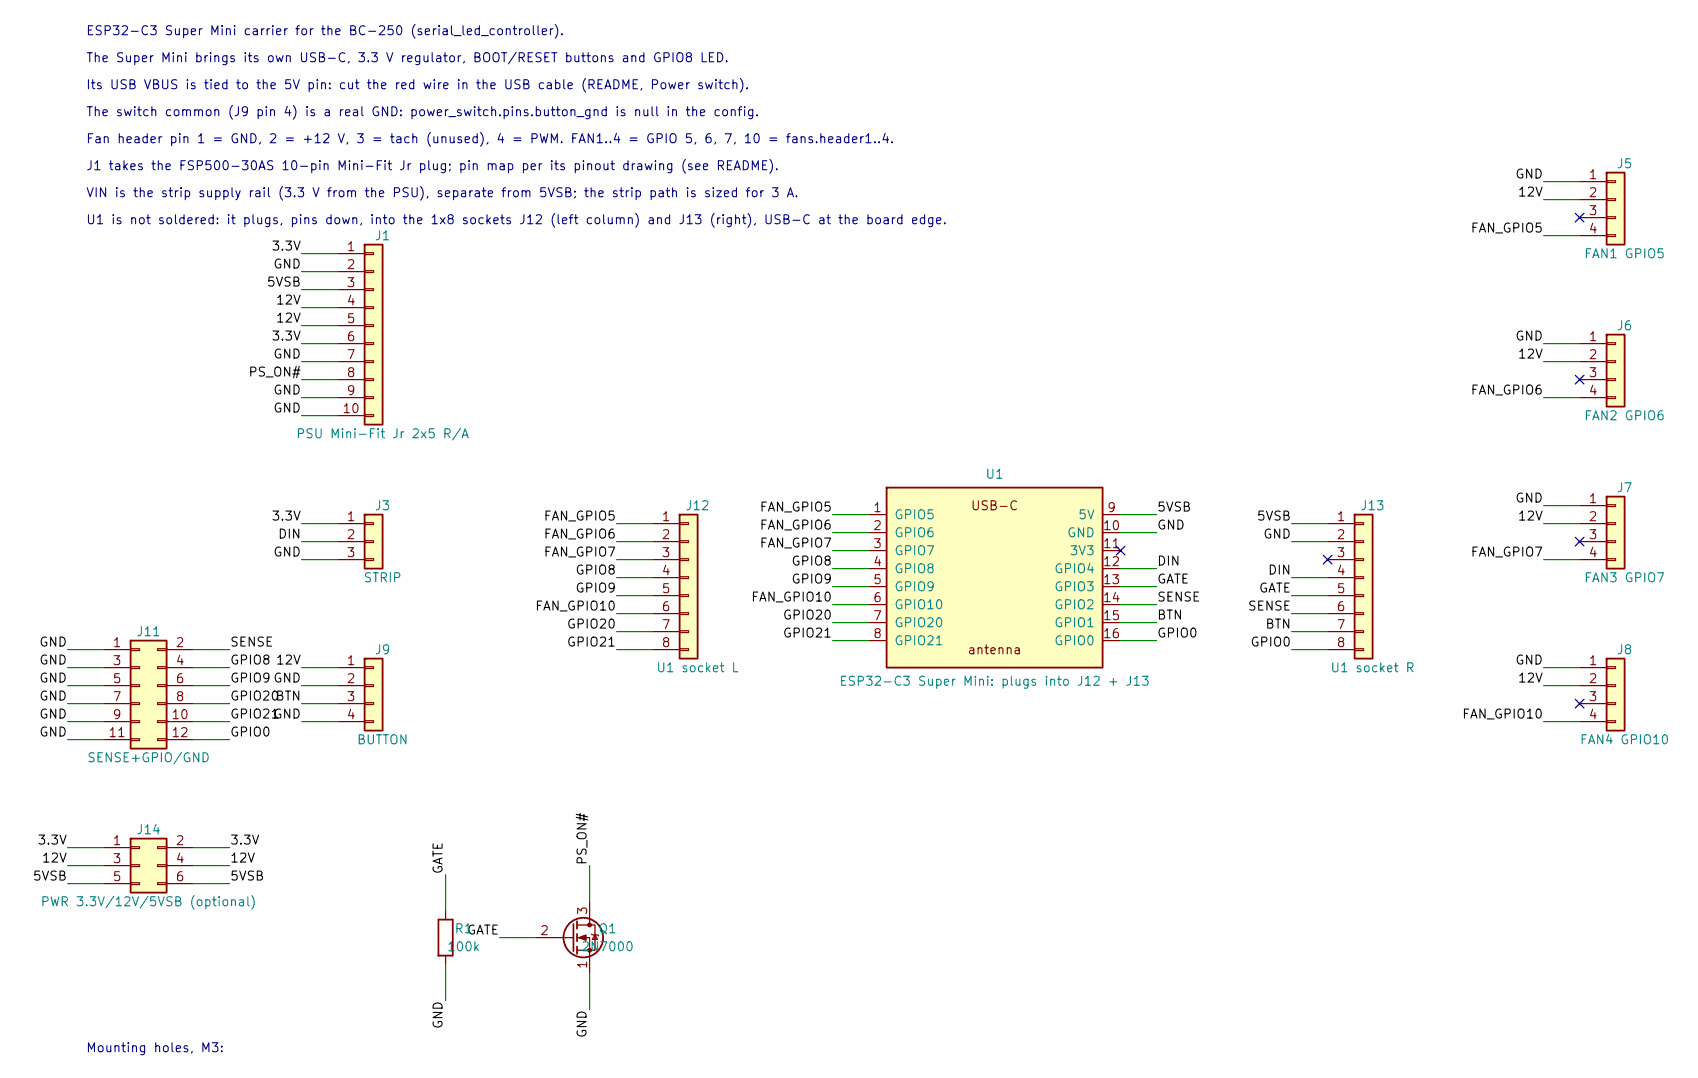
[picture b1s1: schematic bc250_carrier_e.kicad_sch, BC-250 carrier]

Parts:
J1: PSU Mini-Fit Jr 2x5 R/A; Molex_Mini-Fit_Jr_5569-10A2_2x05_P4.20mm_Horizontal
J3: STRIP; JST_VH_B3P-VH_1x03_P3.96mm_Vertical
J5: FAN1 GPIO5; Molex_KK-254_AE-6410-04A_1x04_P2.54mm_Vertical
J6: FAN2 GPIO6; Molex_KK-254_AE-6410-04A_1x04_P2.54mm_Vertical
J7: FAN3 GPIO7; Molex_KK-254_AE-6410-04A_1x04_P2.54mm_Vertical
J8: FAN4 GPIO10; Molex_KK-254_AE-6410-04A_1x04_P2.54mm_Vertical
J9: BUTTON; JST_XH_B4B-XH-A_1x04_P2.50mm_Vertical
J11: SENSE+GPIO/GND; PinHeader_2x06_P2.54mm_Vertical
J12: U1 socket L; PinSocket_1x08_P2.54mm_Vertical
J13: U1 socket R; PinSocket_1x08_P2.54mm_Vertical
J14: PWR 3.3V/12V/5VSB (optional); PinHeader_2x03_P2.54mm_Vertical
Q1: 2N7000; TO-92_Inline_Wide
R1: 100k; R_Axial_DIN0207_L6.3mm_D2.5mm_P7.62mm_Horizontal
U1: ESP32-C3 Super Mini: plugs into J12 + J13

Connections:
3.3V: J1.1, J1.6, J3.1, J14.1, J14.2
5VSB: J1.3, J13.1, J14.5, J14.6, U1.9 (5V)
12V: J1.4, J1.5, J5.2, J6.2, J7.2, J8.2, J9.1, J14.3, J14.4
BTN: J9.3, J13.7, U1.15 (GPIO1)
DIN: J3.2, J13.4, U1.12 (GPIO4)
FAN_GPIO5: J5.4, J12.1, U1.1 (GPIO5)
FAN_GPIO6: J6.4, J12.2, U1.2 (GPIO6)
FAN_GPIO7: J7.4, J12.3, U1.3 (GPIO7)
FAN_GPIO10: J8.4, J12.6, U1.6 (GPIO10)
GATE: J13.5, Q1.2 (G), R1.1, U1.13 (GPIO3)
GND: J1.2, J1.7, J1.9, J1.10, J3.3, J5.1, J6.1, J7.1, J8.1, J9.2, J9.4, J11.1, J11.3, J11.5, J11.7, J11.9, J11.11, J13.2, Q1.1 (S), R1.2, U1.10 (GND)
GPIO0: J11.12, J13.8, U1.16 (GPIO0)
GPIO8: J11.4, J12.4, U1.4 (GPIO8)
GPIO9: J11.6, J12.5, U1.5 (GPIO9)
GPIO20: J11.8, J12.7, U1.7 (GPIO20)
GPIO21: J11.10, J12.8, U1.8 (GPIO21)
PS_ON#: J1.8, Q1.3 (D)
SENSE: J11.2, J13.6, U1.14 (GPIO2)

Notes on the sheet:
ESP32-C3 Super Mini carrier for the BC-250 (serial_led_controller).
The Super Mini brings its own USB-C, 3.3 V regulator, BOOT/RESET buttons and GPIO8 LED.
U1 is not soldered: it plugs, pins down, into the 1x8 sockets J12 (left column) and J13 (right), USB-C at the board edge.
Its USB VBUS is tied to the 5V pin: cut the red wire in the USB cable (README, Power switch).
The switch common (J9 pin 4) is a real GND: power_switch.pins.button_gnd is null in the config.
Fan header pin 1 = GND, 2 = +12 V, 3 = tach (unused), 4 = PWM. FAN1..4 = GPIO 5, 6, 7, 10 = fans.header1..4.
J1 takes the FSP500-30AS 10-pin Mini-Fit Jr plug; pin map per its pinout drawing (see README).
VIN is the strip supply rail (3.3 V from the PSU), separate from 5VSB; the strip path is sized for 3 A.
Mounting holes, M3:

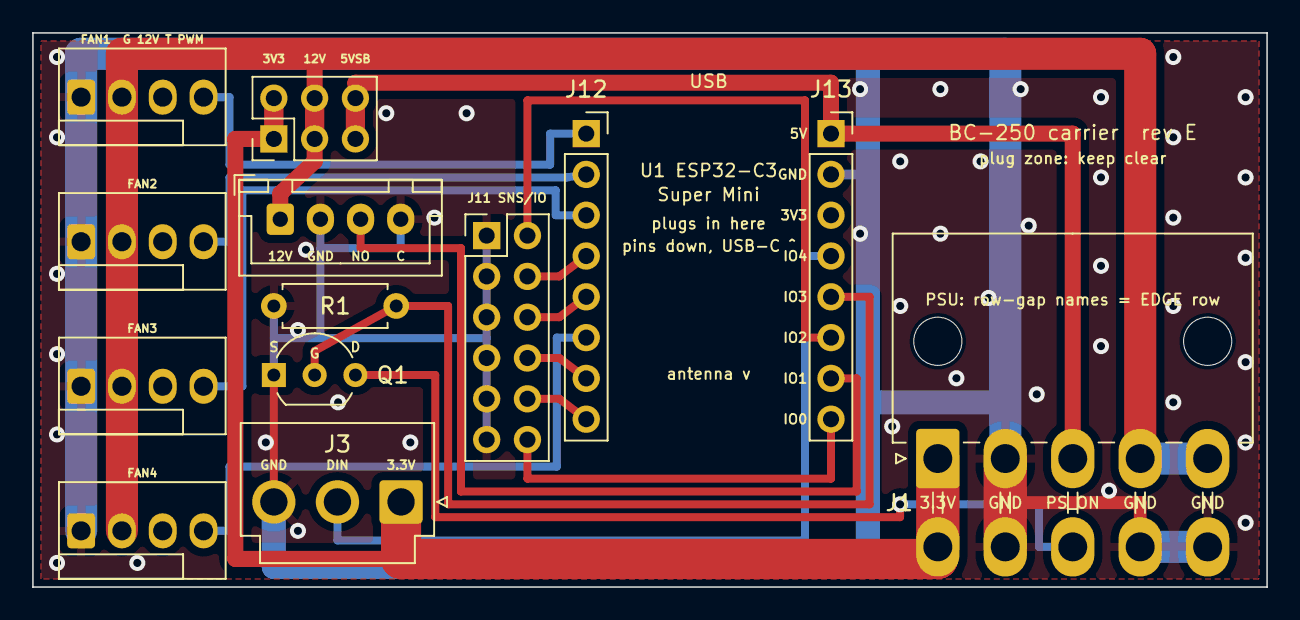
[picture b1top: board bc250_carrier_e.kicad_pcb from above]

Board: 2 copper layers, 76.8 x 34.5 mm, 13 parts (0 on the bottom side), 18 nets.

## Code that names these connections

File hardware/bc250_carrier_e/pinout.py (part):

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    sml, smr = pad('J12', 1)[0], pad('J13', 1)[0]
    top, bot = g.SM_CY - g.SM_L / 2, g.SM_BOT
    dr.rectangle([P(sml + 1.3, top), P(smr - 1.3, bot)], fill=(0, 0, 0, 120))
    short_left = {'GPIO5': 'IO5  FAN1', 'GPIO6': 'IO6  FAN2', 'GPIO7': 'IO7  FAN3', 'GPIO8': 'IO8  J11',
                  'GPIO9': 'IO9  J11', 'GPIO10': 'IO10 FAN4', 'GPIO20': 'IO20 WAKE', 'GPIO21': 'IO21 J11'}
    short_right = {'5V': '5VSB', 'GND': 'GND', '3V3': 'n/c 3V3', 'GPIO4': 'DIN  IO4', 'GPIO3': 'GATE IO3',
                   'GPIO2': 'SNS  IO2', 'GPIO1': 'BTN  IO1', 'GPIO0': 'J11  IO0'}
    for i, nm in enumerate(g.SM_LEFT):
        x, y = pad('J12', i + 1)
        text(x + 1.5, y, short_left[nm], 0.72, net_color(g.NETS.get(('J12', str(i + 1)))), 'lm', True)
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    ty = by1 + 1.4
    text(bx0 - ML + 1.0, ty, 'U1 left column, top → bottom', 0.85, C_TXT, 'lm', True, stroke=False)
    text(bx0 - ML + 23.5, ty, 'U1 right column, top → bottom', 0.85, C_TXT, 'lm', True, stroke=False)
    role_left = ['GPIO5 → FAN1 PWM (J5)', 'GPIO6 → FAN2 PWM (J6)', 'GPIO7 → FAN3 PWM (J7)',
                 'GPIO8 → J11 p4 · blue LED · strap', 'GPIO9 → J11 p6 · BOOT strap',
                 'GPIO10 → FAN4 PWM (J8)', 'GPIO20 → J11 p8 · wake (OpenPuck)', 'GPIO21 → J11 p10 · U0TXD']
    role_right = ['5V ← 5VSB (standby, always on)', 'GND', '3V3: module output, unused',
                  'GPIO4 → DIN, strip data (J3)', 'GPIO3 → GATE of Q1 → PS_ON#',
                  'GPIO2 ← SENSE, TPMS1 pin 9 (J11 p2)', 'GPIO1 ← button NO (J9 pin 3)', 'GPIO0 → J11 p12']
    for i in range(8):
        cl = net_color(g.NETS.get(('J12', str(i + 1))))
        cr = net_color(g.NETS.get(('J13', str(i + 1))))
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        text(bx0 - 1.0 - f.getlength(s_in) / SCALE - 2.0, y, s_out, 0.95, net_color(outer), 'rm')
        dr.line([P(bx0 - 0.6, y), P(g.J11_X0 - 0.9, y)], fill=(120, 120, 120, 160), width=1)
    oy = g.J11Y[-1] + 2.7
    text(bx0 - 1.0, oy, 'OpenPuck:  017 → J11 pin 8 (GPIO20)', 0.9, C_GPIO, 'rm', True)
    text(bx0 - 1.0, oy + 1.5, 'GND → J11 pin 7 (GND)', 0.9, C_GND, 'rm', True)
    text(bx0 - 1.0, oy + 3.0, 'BAT → J14 pin 5 or 6 (5VSB)', 0.9, C_5VSB, 'rm', True)
    text(bx0 - 1.0, oy + 4.4, "the puck's USB cable stays intact", 0.75, C_DIM, 'rm')
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                     width=2)

    # J3: strip
    for pin, lab in ((1, '3.3V'), (2, 'DIN (GPIO4)'), (3, 'GND')):
        x, y = pad('J3', pin)
        text(x, y - 2.75, lab, 0.72, net_color(g.NETS[('J3', str(pin))]), 'mm', True)
    text(g.VH_X[1], g.VH_Y - 4.15, 'J3  STRIP  JST-VH · pin 1 ▷ = 3.3V · 3 A', 0.72, C_TXT, 'mm', True)
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        text(x1 + 1.5 * g.FAN_P, y + 1.9, f'J{5 + k} FAN{k + 1} · {gp}', 0.62, C_GPIO, 'mm', True)

    # J9 button: below the board edge
    for pin, lab in ((1, '1 ▷ 12V  ring LED +'), (2, '2: GND  ring LED −'), (3, '3: NO → GPIO1'), (4, '4: C = GND')):
        x, y = pad('J9', pin)
        vtext(x, by1 + 0.6, lab, 0.85, net_color(g.NETS.get(('J9', str(pin)))), top=True, bold=True)
    cy = by1 + 13.4   # group captions under the vertical pad labels
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    for pin, lab in ((1, 'S'), (2, 'G'), (3, 'D')):
        x, y = pad('Q1', pin)
        text(x, y - 1.35, lab, 0.62, net_color(g.NETS.get(('Q1', str(pin)))), 'mm', True)
    text(g.Q1_G, g.Q1_Y + 1.75, 'Q1 2N7000: S GND · G ← GPIO3 · D → PS_ON#', 0.55, C_PSON, 'mm', True)
    text((g.R1_P1[0] + g.R1_P2[0]) / 2, g.R1_Y - 1.5, 'R1 100 kΩ', 0.62, C_PSON)

    # ---- title, legend, notes ----------------------------------------------
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    text(lx, ly, 'colours:', 0.95, C_TXT, 'lm', True, stroke=False)
    off = 7.5
    for n, c in (('12V', C_12V), ('5VSB', C_5VSB), ('3.3V', C_33), ('GND', C_GND), ('PS_ON# / gate', C_PSON),
                 ('strip DIN', C_DIN), ('GPIO / signal', C_GPIO)):
        text(lx + off, ly, n, 0.95, c, 'lm', True, stroke=False)
        off += font(0.95, True).getlength(n) / SCALE + 3.0
    dr.line([P(bx1 - 10, ly), P(bx1, ly)], fill=(255, 255, 255), width=3)
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        'module (and an OpenPuck on J14) at all times. The rails have their own header, J14, beside the PSU header, away from the GPIOs on J11.',
        "The C3 module's USB VBUS is tied to its 5V pin, so cut the red wire in the MODULE's USB cable (README, "
        "Power switch). The puck's cable stays whole.",
        'Q1: flat face per the silkscreen outline, pins S G D left to right; R1 is its 100 kΩ gate pull-down.',
        'Fan headers J5–J8: stacked down the left edge, pins G · 12V · T · PWM left to right; lock ramp (over G · 12V · T) facing down, tach unconnected.',
        'config.json  power_switch.pins: ps_on 3 · button 1 · button_gnd null · sense 2 · led 8 · wake 20 (null '
        'without a puck).  fans.header1..4 = FAN1..4.  strip.pin 4.',
    ]
    for i, s in enumerate(notes):
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
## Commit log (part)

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2026-06-10 Initial commit: WS2812B LED controller for AMD BC-250 with ESP32 serial receiver
2026-06-10 gpu load: read average_gfx_activity from gpu_metrics like MangoHud
    The BC-250's cyan skillfish driver doesn't implement the GPU_LOAD
    sensor, so gpu_busy_percent never appears and the load effect's GPU
    bar stayed at zero. MangoHud works there because it parses the binary
    gpu_metrics SMU table instead.
    Add a gpu_metrics parser (format 1/2/3 layouts per kgd_pp_interface.h,
    0xffff = unpopulated, sticky centipercent divide) and a shared
2026-06-12 load: light pixels at their center, not their far edge
    The outermost pixel on each side required the smoothed load to reach
    exactly 1.0, which a sensor that rarely reports a flat 100% and
    exponential smoothing that only converges toward its target never
    produce — so the bar could never show full. Center-based thresholds
    make the last pixel light at the conventional midpoint (90% on a
    10-LED strip) instead.
2026-06-12 steam_download: drop the file-driven source, rename from progress
    Writing /tmp/led-progress by hand was cumbersome and the Steam
    tracking covers the real use case, so the effect now follows
    steam::downloads() directly and the file rule is gone. With Steam the
    only source, "progress" undersold the effect — renamed to
    steam_download (the old generic file-driven version remains in
    history at b25a8a1 if ever needed again). Bar and done-pulse colors
2026-06-15 esp32: don't auto-play breathe after a finite power-on effect
    The receiver hardcoded a handoff to breathe when a finite power-on effect
    (e.g. boot) finished — an unconfigurable behavior baked into the firmware.
    Drop it: the power-on slot just plays its configured effect. A looping
    effect runs until the host connects; a finite one plays once and holds its
    last frame. boot-then-idle is now an explicit choice (a looping power-on
    effect, or one effect that does both).
2026-06-15 boot: simplify the power-on to a center-out bloom
    The three-act sequence (sparking sweep, rippling charge-up, white
    flash-out) was over the top. Replace it with one gesture: the charge
    color blooms outward from the center to both ends, holds briefly, then
    fades to black. Antialiased front keeps it smooth on the long strip.
    Drops the now-unused flash_color, sparks, and trail buffer; keeps
    duration_seconds/color and the finished() handoff.
2026-06-15 restructure by execution target; reuse the parser for build config
    - group source into shared/ (daemon + firmware), host/ (daemon-only),
    firmware/, and vendor/; includes stay path-less so the receiver's
    flat copy is unaffected and the host build just adds -I per dir
    - add `led --config-get <config> <path>` and use it in the Makefile
    instead of sed-scraping JSON, so build values can't drift from how
    the daemon reads the same file
2026-06-15 steam_download: raise track floor so the faint bar survives the lut
    The unfilled-track floor of 0.15 was below the visibility threshold of
    the host's color lut: at the default gamma 2.2 and 20% brightness the
    gamma curve crushes it to a single unit of blue (0,0,1), so an
    empty/near-empty bar read as a dead-black strip. 0.30 maps to a dim but
    visible blue (~8% of the filled bar).
2026-06-15 tools: measure network RX + exact download-cache bytes, not the manifest
    The manifest counters stay frozen during the download on this box, so
    sample the real effects of a transfer instead: total network RX bytes
    and the exact (du -sb) size of steamapps/downloading/<appid>. This shows
    whether data is actually flowing and which signal the daemon should
    track, rather than reading placeholder byte fields.
2026-06-15 steam_download: flow the filled bar; detect pause via the download cache
    Two improvements:
    - effect: a gentle crest now flows along the filled bar toward the head
    so an active download reads as alive rather than static. Tunable via
    flow_speed / flow_depth (set flow_depth 0 to disable).
    - detection: 'actively downloading' now tracks movement of the
    steamapps/downloading/ chunk cache instead of the manifest byte
2026-06-15 steam: drive live percent from the download cache, not the stale manifest
    The bar froze mid-download and only jumped on pause: percent came from
    the manifest's BytesDownloaded, which Steam rewrites only ~once a minute
    (and flushes on pause), so it sat stale between writes. The download
    cache grows in real time, so compute the live downloaded figure as
    max(cache, manifest BytesDownloaded) over the stable BytesToDownload
    total, with a high-water mark so a cache flush to disk can't make the
2026-06-15 steam_download: pulse the bar instead of rippling it
    Filled LEDs now hold steady at full; once per flow_period a single
    crest sweeps start -> head and then rests, so the fill reads cleanly
    between pulses instead of constantly dimming. Replaces flow_speed with
    flow_period.
2026-06-16 boot/shutdown: CRT-style power on/off effects
    Shutdown collapses the lit strip inward to a white-hot point that fades
    out with phosphor persistence — a fast snap with a lingering glow.
    Boot mirrors it: a center point ignites, whips outward into a scan line,
    resolves to the body color, holds with a faint scanline shimmer, then
    fades to black. Fast to come up, long-lived hold.
    Both gain a configurable flash_color; default durations bumped to give
2026-06-18 effects: smoother, less static visuals + crossfade between effects
    load: soft-tipped bars washed with aurora-style cool-hue curtains and a
    brightness shimmer, so a GPU pinned at 100% keeps drifting instead of
    sitting as a static block; drops the thermal green->red ramp.
    cpu_temp: soft tip + slow shimmer (thermal ramp kept; color means temp).
    fire: gentler flicker blended with a slow flowing drift.
    steam_download: shallow uniform breath between flow sweeps.
2026-06-19 load: mirror aurora wash/shimmer about center so halves flow symmetrically
    The bars already grow from the center outward (CPU toward pixel 0, GPU
    toward the last pixel), but the hue curtains and brightness shimmer were
    keyed off a global i/leds coordinate that swept straight across the whole
    strip in one screen direction. That made the GPU side appear to pulse the
    'wrong' way relative to the CPU side. Key the wash/shimmer off the per-side
    outward distance instead so both halves flow symmetrically.
2026-06-22 effects: expose frame_ms so frame rate is configurable per-effect or globally
    Add setFrameDelay() to the Effect base: each effect resolves frame_ms in
    init() (rule settings first, then top-level config as a global default,
    else its own built-in). Defaults unchanged -- 33ms for the steady visuals,
    16ms for the one-shot/transition ones. cycle keeps delegating to its sub.
    Effects that integrate state per frame (load, comet, twinkle,
    steam_download) read frameDelayMs() as their dt, so the one value drives
2026-06-22 make: add install-config to force-deploy and apply the repo config
    install leaves an existing /etc config untouched so a deploy can't
    clobber local tweaks; install-config overwrites it and try-restarts the
    daemon to apply, for when the repo config is the source of truth.
2026-06-23 esp32: record/replay boot+shutdown instead of on-device effects
    The receiver no longer compiles or renders any effect code. The daemon
    renders the configured power-on/shutdown effects through its own Strip
    (so the pixels are byte-identical to live hardware output), captures the
    frames, and streams them; the receiver stores each in LittleFS and
    replays them. Iterating on the boot/shutdown animations no longer needs
    a reflash — edit config, restart the daemon, see it next power cycle.
2026-06-24 examples: add button-spread power on/off config snippet
    A copy-paste esp32 block wiring the experimental button_on/button_off
    effects into power_on/shutdown, with notes on the record_seconds math
    that keeps the intro->breathe handoff and the breathe loop seamless.
2026-06-25 effects: add lava metaball effect
    A 'lava lamp' of soft metaball blobs that drift at constant velocity and
    bounce only at the strip ends (never reversing mid-strip). Overlapping
    fields add into brighter, hotter spots and blend palette colors; a
    sliding per-blob palette window cycles the scene through every color.
    - factor reflect() out of pingpong() in motion.hpp
    - vivid default palette, default radius 0.2 (blobs fill the strip at
2026-06-30 steam_download: clear progress bar with fluid pulse + ripple
    Rework the effect around bar legibility first: a dim cool unfilled track,
    a bright warm magenta->gold fill whose hottest pixel is always the leading
    edge, and a bright pulsing head glow marking how far along the download is.
    Motion stays confined to [0,head] -- shallow waves flow toward the head and
    each percent bump flares the bar and rushes a bright crest up to the front.
    Add the chosen look to config.json's steam_dl rule settings.
2026-06-30 firmware: add inert LED_SELFTEST to prove the strip path on-chip
    A compile-time-disabled diagnostic: when LED_SELFTEST is defined, setup()
    drives the strip red/green/blue directly on a wired pin, bypassing the host
    link and recording replay. Isolates 'C3 + lib + initStrip/show work' from
    'no daemon frames are arriving'. Inert by default (the define is commented).
2026-06-30 flash: let configured serial port win over auto-detection
    Detection picked the first /dev/tty* arduino-cli listed (e.g. /dev/ttyACM0)
    and overrode the port pinned in config, so a C3 set to /dev/ttyACM1 got
    flashed to the wrong device. Resolution is now override > config > detected >
    default for PORT, and the FQBN is fingerprinted for the resolved PORT rather
    than the first listed board. Detection stays as the fallback for a fresh
    setup with no configured port.
2026-06-30 flash: one-step compile+upload; stable /dev/led-controller via udev rule
    Two fixes:
    - Upload was failing with 'tools/{build.partitions}.csv: no such file' because
    'upload --input-dir' doesn't carry the board's build properties, so the
    partition placeholder never expands. Flash now does 'arduino-cli compile
    --upload' in a single invocation, which keeps full build context (and also
    works the same under sudo, fixing the earlier 'cannot stat partitions.csv').
2026-06-30 firmware: ship sketch-local partitions.csv to bypass broken {build.partitions} lookup
    arduino-esp32 3.3.x leaves the literal {build.partitions} unexpanded in the
    tools/partitions/{build.partitions}.csv copy once any FQBN menu option (e.g.
    CDCOnBoot) is set, and neither PartitionScheme=default nor --build-property
    build.partitions=default overrides it. A partitions.csv in the sketch folder is
    copied directly by the platform, so that lookup never runs. Standard default
    4MB layout with the 'spiffs' partition the firmware's LittleFS recordings use.
